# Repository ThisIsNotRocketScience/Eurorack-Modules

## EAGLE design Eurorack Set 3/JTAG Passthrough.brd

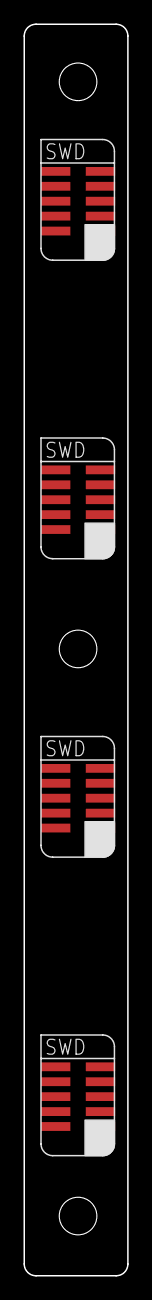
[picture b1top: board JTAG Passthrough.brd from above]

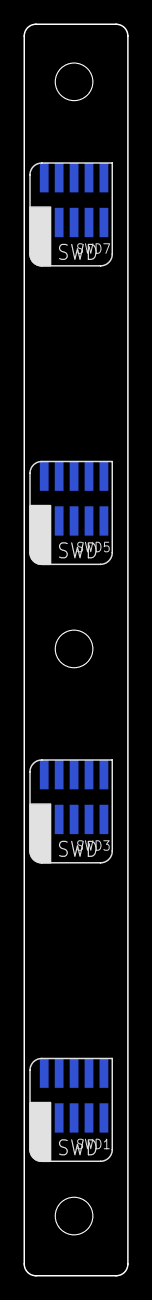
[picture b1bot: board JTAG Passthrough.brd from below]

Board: 2 copper layers, 8.8 x 106.5 mm, 9 parts (4 on the bottom side), 40 nets, no tracks yet.

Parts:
SWD1, SWD3, SWD5, SWD7: CORTEX_SWD; M50-3600542
SWD2, SWD4, SWD6, SWD8: CORTEX_SWDVERT_HOLE; SWD_VERTICAL_WITHHOLE
U$2: EURORACK_PCB2HP; EURORACK2HPPCB

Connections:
unnamed: SWD1.1, SWD2.1
unnamed: SWD1.2, SWD2.2
unnamed: SWD1.3, SWD2.3
unnamed: SWD1.4, SWD2.4
unnamed: SWD1.5, SWD2.5
unnamed: SWD1.6, SWD2.6
unnamed: SWD1.7, SWD2.7
unnamed: SWD1.8, SWD2.8
unnamed: SWD1.9, SWD2.9
unnamed: SWD1.10, SWD2.10
unnamed: SWD3.1, SWD4.1
unnamed: SWD3.2, SWD4.2
unnamed: SWD3.3, SWD4.3
unnamed: SWD3.4, SWD4.4
unnamed: SWD3.5, SWD4.5
unnamed: SWD3.6, SWD4.6
unnamed: SWD3.7, SWD4.7
unnamed: SWD3.8, SWD4.8
unnamed: SWD3.9, SWD4.9
unnamed: SWD3.10, SWD4.10
unnamed: SWD5.1, SWD6.1
unnamed: SWD5.2, SWD6.2
unnamed: SWD5.3, SWD6.3
unnamed: SWD5.4, SWD6.4
unnamed: SWD5.5, SWD6.5
unnamed: SWD5.6, SWD6.6
unnamed: SWD5.7, SWD6.7
unnamed: SWD5.8, SWD6.8
unnamed: SWD5.9, SWD6.9
unnamed: SWD5.10, SWD6.10
unnamed: SWD7.1, SWD8.1
unnamed: SWD7.2, SWD8.2
unnamed: SWD7.3, SWD8.3
unnamed: SWD7.4, SWD8.4
unnamed: SWD7.5, SWD8.5
unnamed: SWD7.6, SWD8.6
unnamed: SWD7.7, SWD8.7
unnamed: SWD7.8, SWD8.8
unnamed: SWD7.9, SWD8.9
unnamed: SWD7.10, SWD8.10

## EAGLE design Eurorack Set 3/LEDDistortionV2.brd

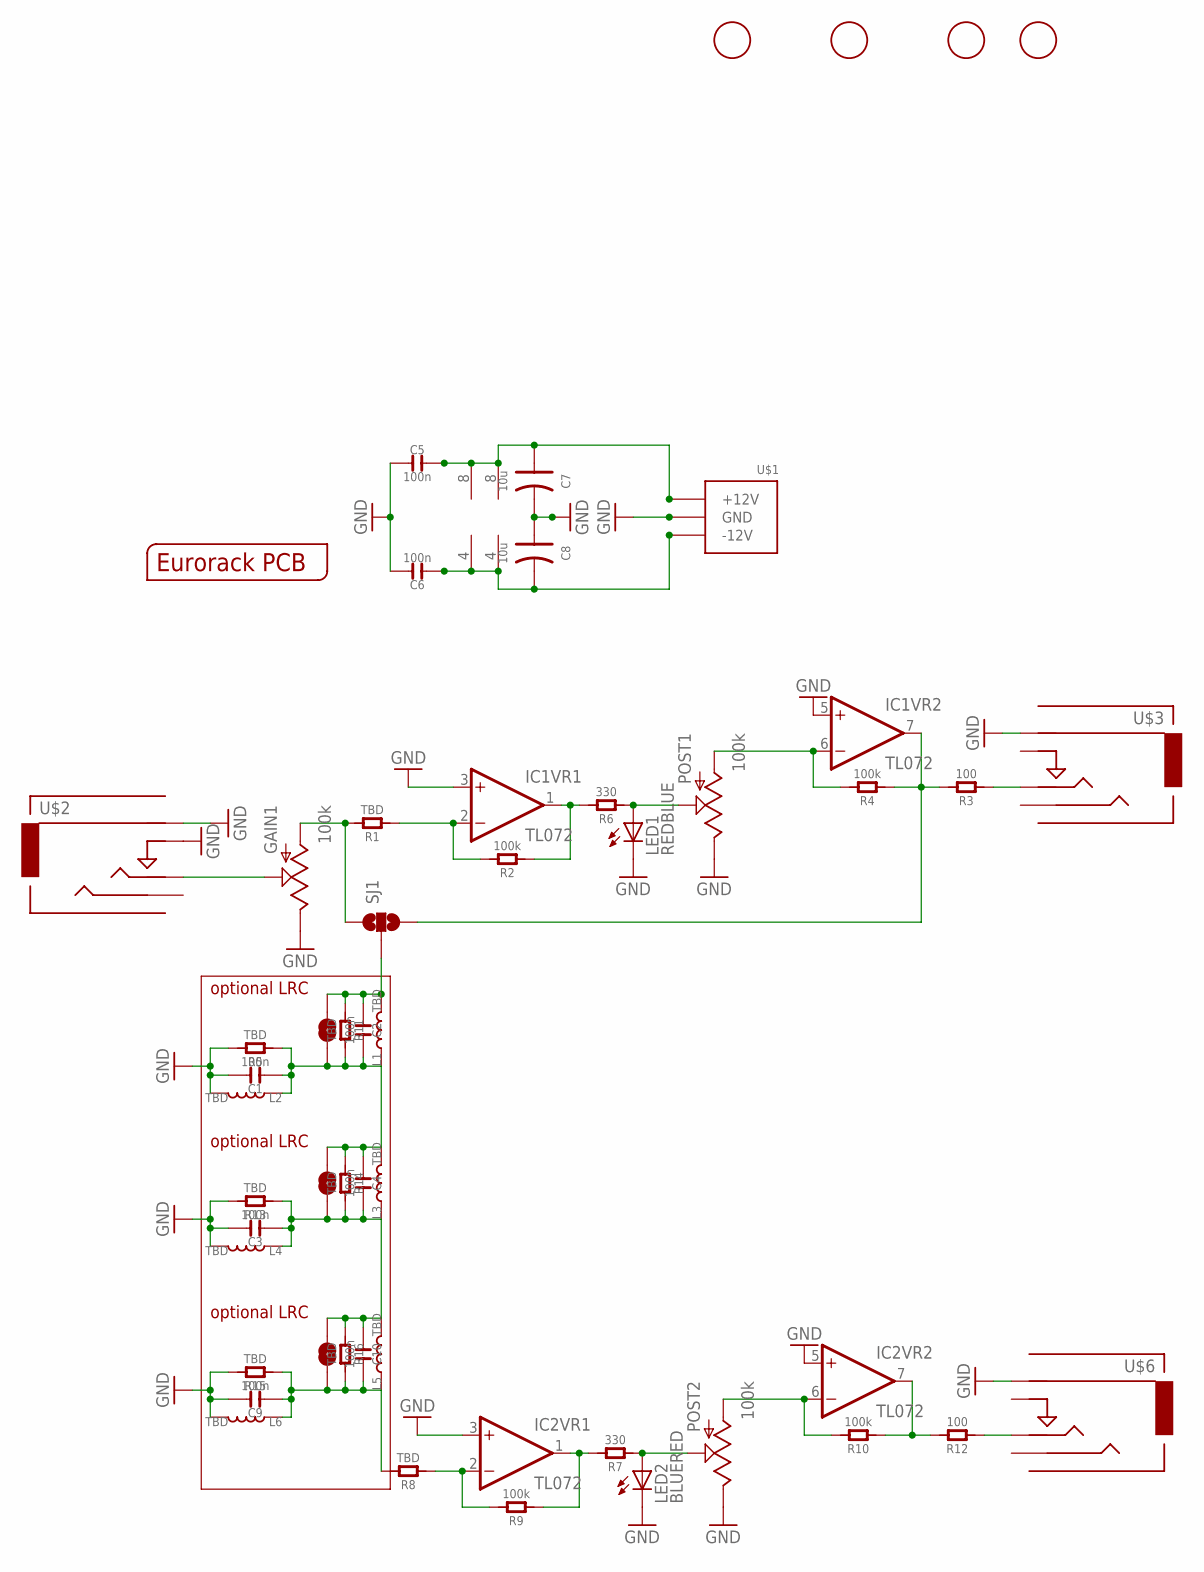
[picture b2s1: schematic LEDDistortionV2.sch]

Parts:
C1, C2, C3, C4, C5, C6, C9, C10: 100n; C0805
C7, C8: 10u; AVX-A
GAIN1: 100k; OG-POTS_ALPS_POT_VERTICAL
IC1, IC2: TL072; SO08
L1, L2, L3, L4, L5, L6: TBD; L0420
LED1: REDBLUE; LED3MM
LED2: BLUERED; LED3MM
POST1, POST2: 100k; OG-POTS_ALPS_POT_VERTICAL
R1, R5, R8, R11, R13, R14, R15, R16: TBD; C0805
R2, R4, R9, R10: 100k; C0805
R3, R12: 100; C0805
R6, R7: 330; C0805
SJ1: SOLDERJUMPER_2WAYPASTE1&2; SJ_3_PASTE1&2
SJ2, SJ3, SJ4: SOLDERJUMPERNC; SJ_2S
U$1: POWER_SIMPLE10; POWER_10
U$2: IN; 3.5MM-JACK-SWITCH-13MM-INPUT
U$3: OUT2; 3.5MM-JACK-SWITCH-13MM-OUTPUT
U$4: EURORACK_PCB4HP; EURORACK4HPPCB
U$5, U$7, U$8, U$9: FIDUCIAL; FIDUCIAL_1MM
U$6: OUT1; 3.5MM-JACK-SWITCH-13MM-OUTPUT

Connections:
GND: C1.2, C3.2, C5.1, C6.2, C7.- (2), C8.+ (1), C9.2, GAIN1.P$1 (E), IC1.3 (+IN), IC1.5 (+IN), IC2.3 (+IN), IC2.5 (+IN), L2.2, L4.2, L6.2, LED1.K (C), LED2.K (C), POST1.P$1 (E), POST2.P$1 (E), R5.2, R13.2, R15.2, U$1.3 (GND), U$1.4 (GND), U$1.5 (GND), U$1.6 (GND), U$1.7 (GND), U$1.8 (GND), U$2.RING@1 (RING), U$2.RING@2 (RING), U$2.SWITCH@1 (SWITCH), U$2.SWITCH@2 (SWITCH), U$3.RING@1 (RING), U$3.RING@2 (RING), U$6.RING@1 (RING), U$6.RING@2 (RING)
unnamed: C2.1, L1.2, R11.1, SJ1.2, SJ2.2
unnamed: LED1.A, POST1.P$2 (S), R6.1
unnamed: GAIN1.P$3 (A), R1.2, SJ1.1
unnamed: IC1.6 (-IN), POST1.P$3 (A), R4.2
unnamed: R3.1, U$3.TIP@1 (TIP), U$3.TIP@2 (TIP)
unnamed: GAIN1.P$2 (S), U$2.TIP@1 (TIP), U$2.TIP@2 (TIP)
unnamed: LED2.A, POST2.P$2 (S), R7.1
unnamed: IC2.6 (-IN), POST2.P$3 (A), R10.2
unnamed: C1.1, C2.2, C4.1, L1.1, L2.1, L3.2, R5.1, R11.2, R14.1, SJ2.1, SJ3.2
unnamed: R12.1, U$6.TIP@1 (TIP), U$6.TIP@2 (TIP)
unnamed: C9.1, C10.2, L5.1, L6.1, R8.2, R15.1, R16.2, SJ4.1
unnamed: C3.1, C4.2, C10.1, L3.1, L4.1, L5.2, R13.1, R14.2, R16.1, SJ3.1, SJ4.2
OP1NEG: IC1.2 (-IN), R1.1, R2.2
OP1NEG1: IC2.2 (-IN), R8.1, R9.2
OP1OUT: IC1.1 (OUT), R2.1, R6.2
OP1OUT1: IC2.1 (OUT), R7.2, R9.1
OP2OUT: IC1.7 (OUT), R3.2, R4.1, SJ1.3
OP2OUT1: IC2.7 (OUT), R10.1, R12.2
VNEG: C6.1, C8.- (2), IC1.4 (V-), IC2.4 (V-), U$1.1 (-12V), U$1.2 (-12V)
VPOS: C5.2, C7.+ (1), IC1.8 (V+), IC2.8 (V+), U$1.9 (+12V), U$1.10 (+12V)

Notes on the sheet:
optional LRC

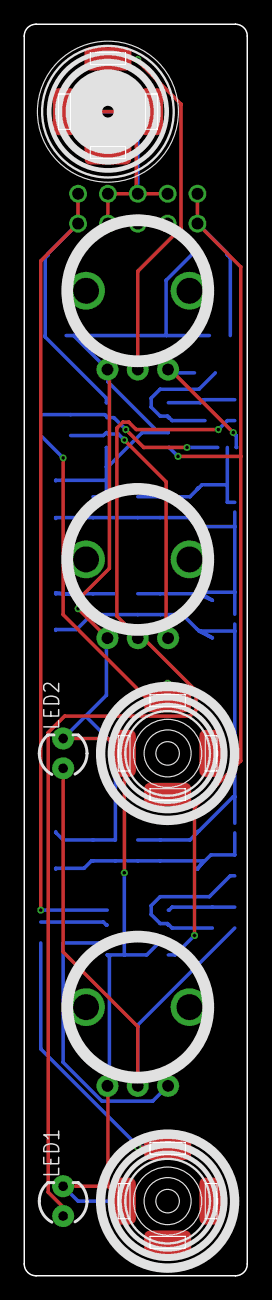
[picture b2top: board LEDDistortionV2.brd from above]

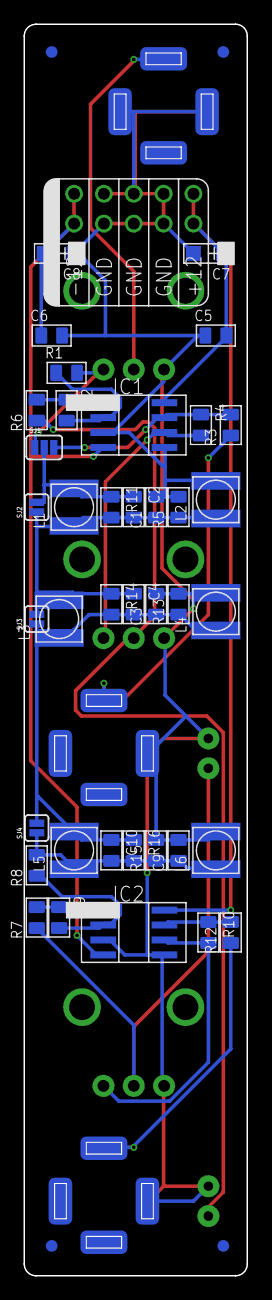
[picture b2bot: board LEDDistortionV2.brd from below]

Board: 2 copper layers, 19.0 x 106.5 mm, 52 parts (43 on the bottom side), 21 nets.

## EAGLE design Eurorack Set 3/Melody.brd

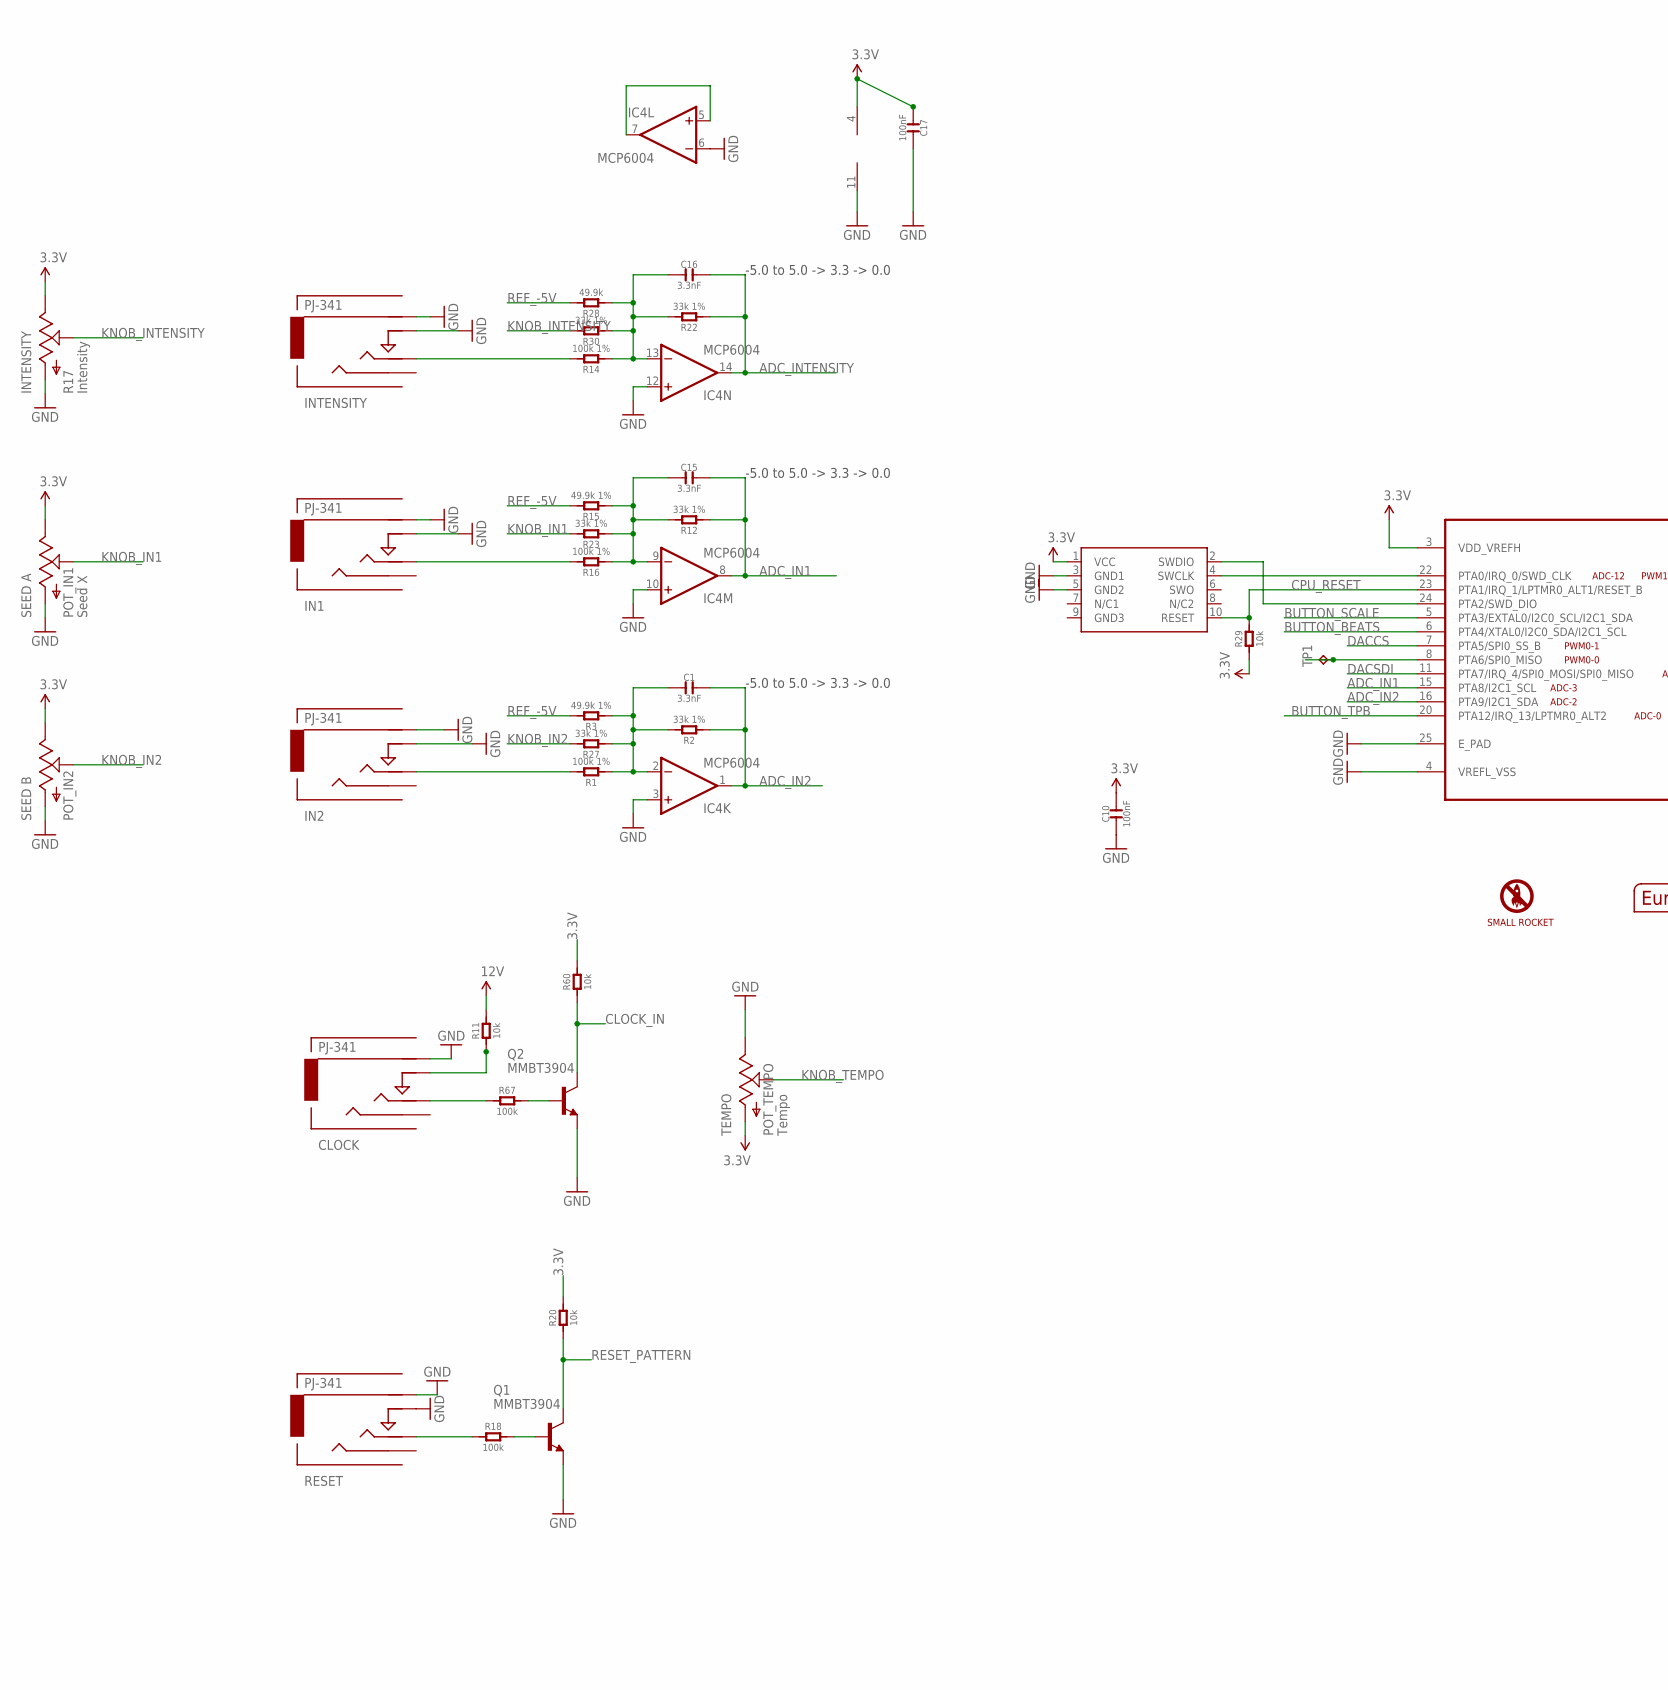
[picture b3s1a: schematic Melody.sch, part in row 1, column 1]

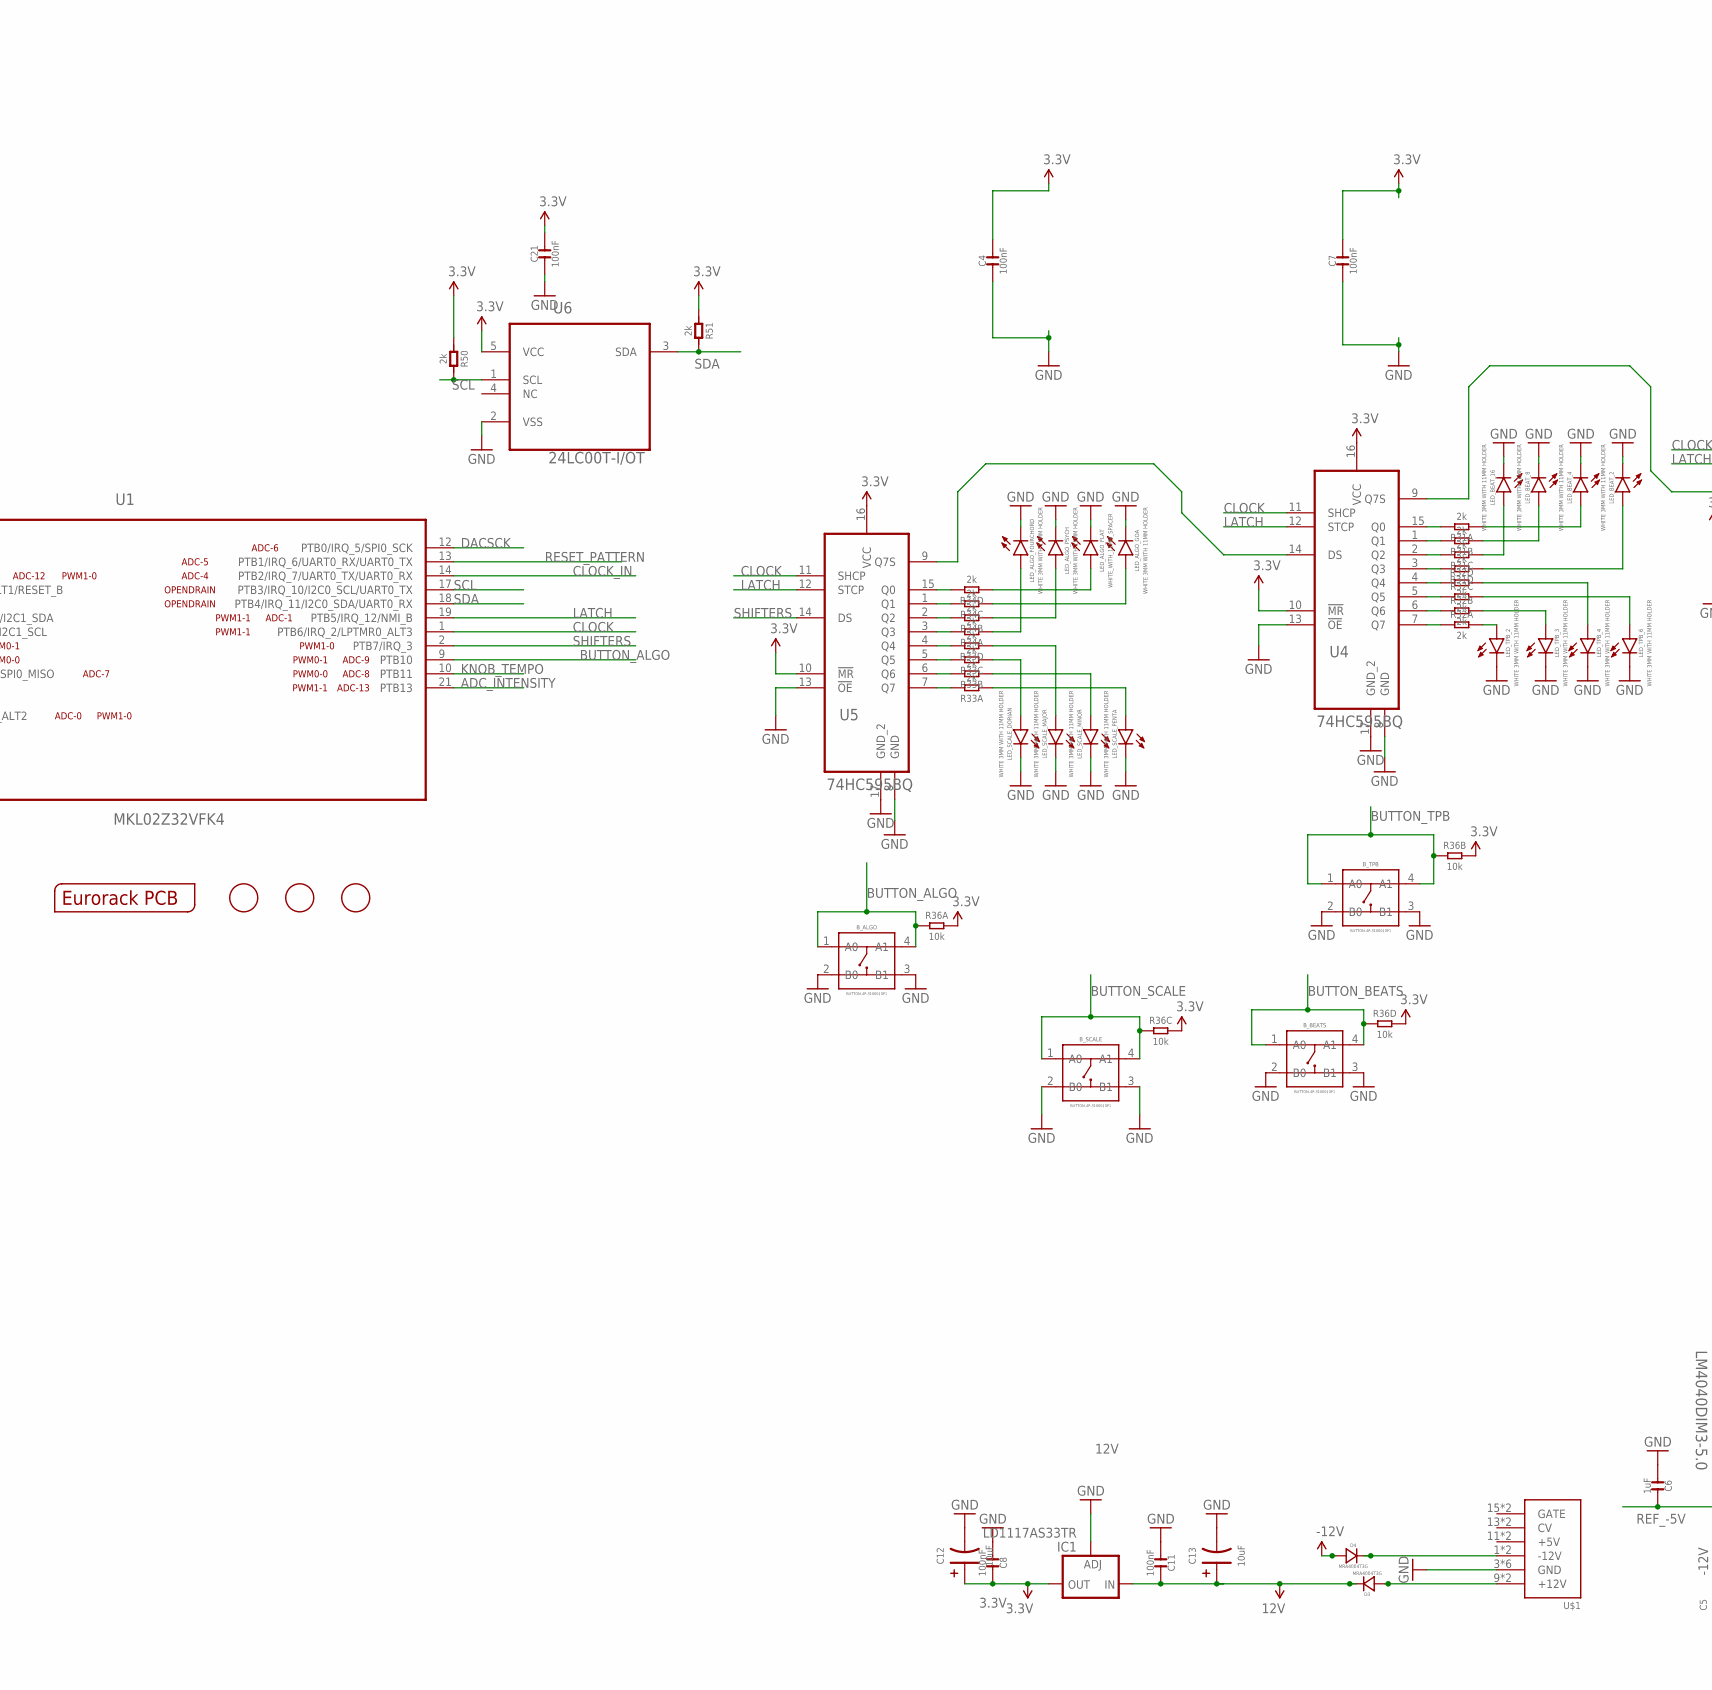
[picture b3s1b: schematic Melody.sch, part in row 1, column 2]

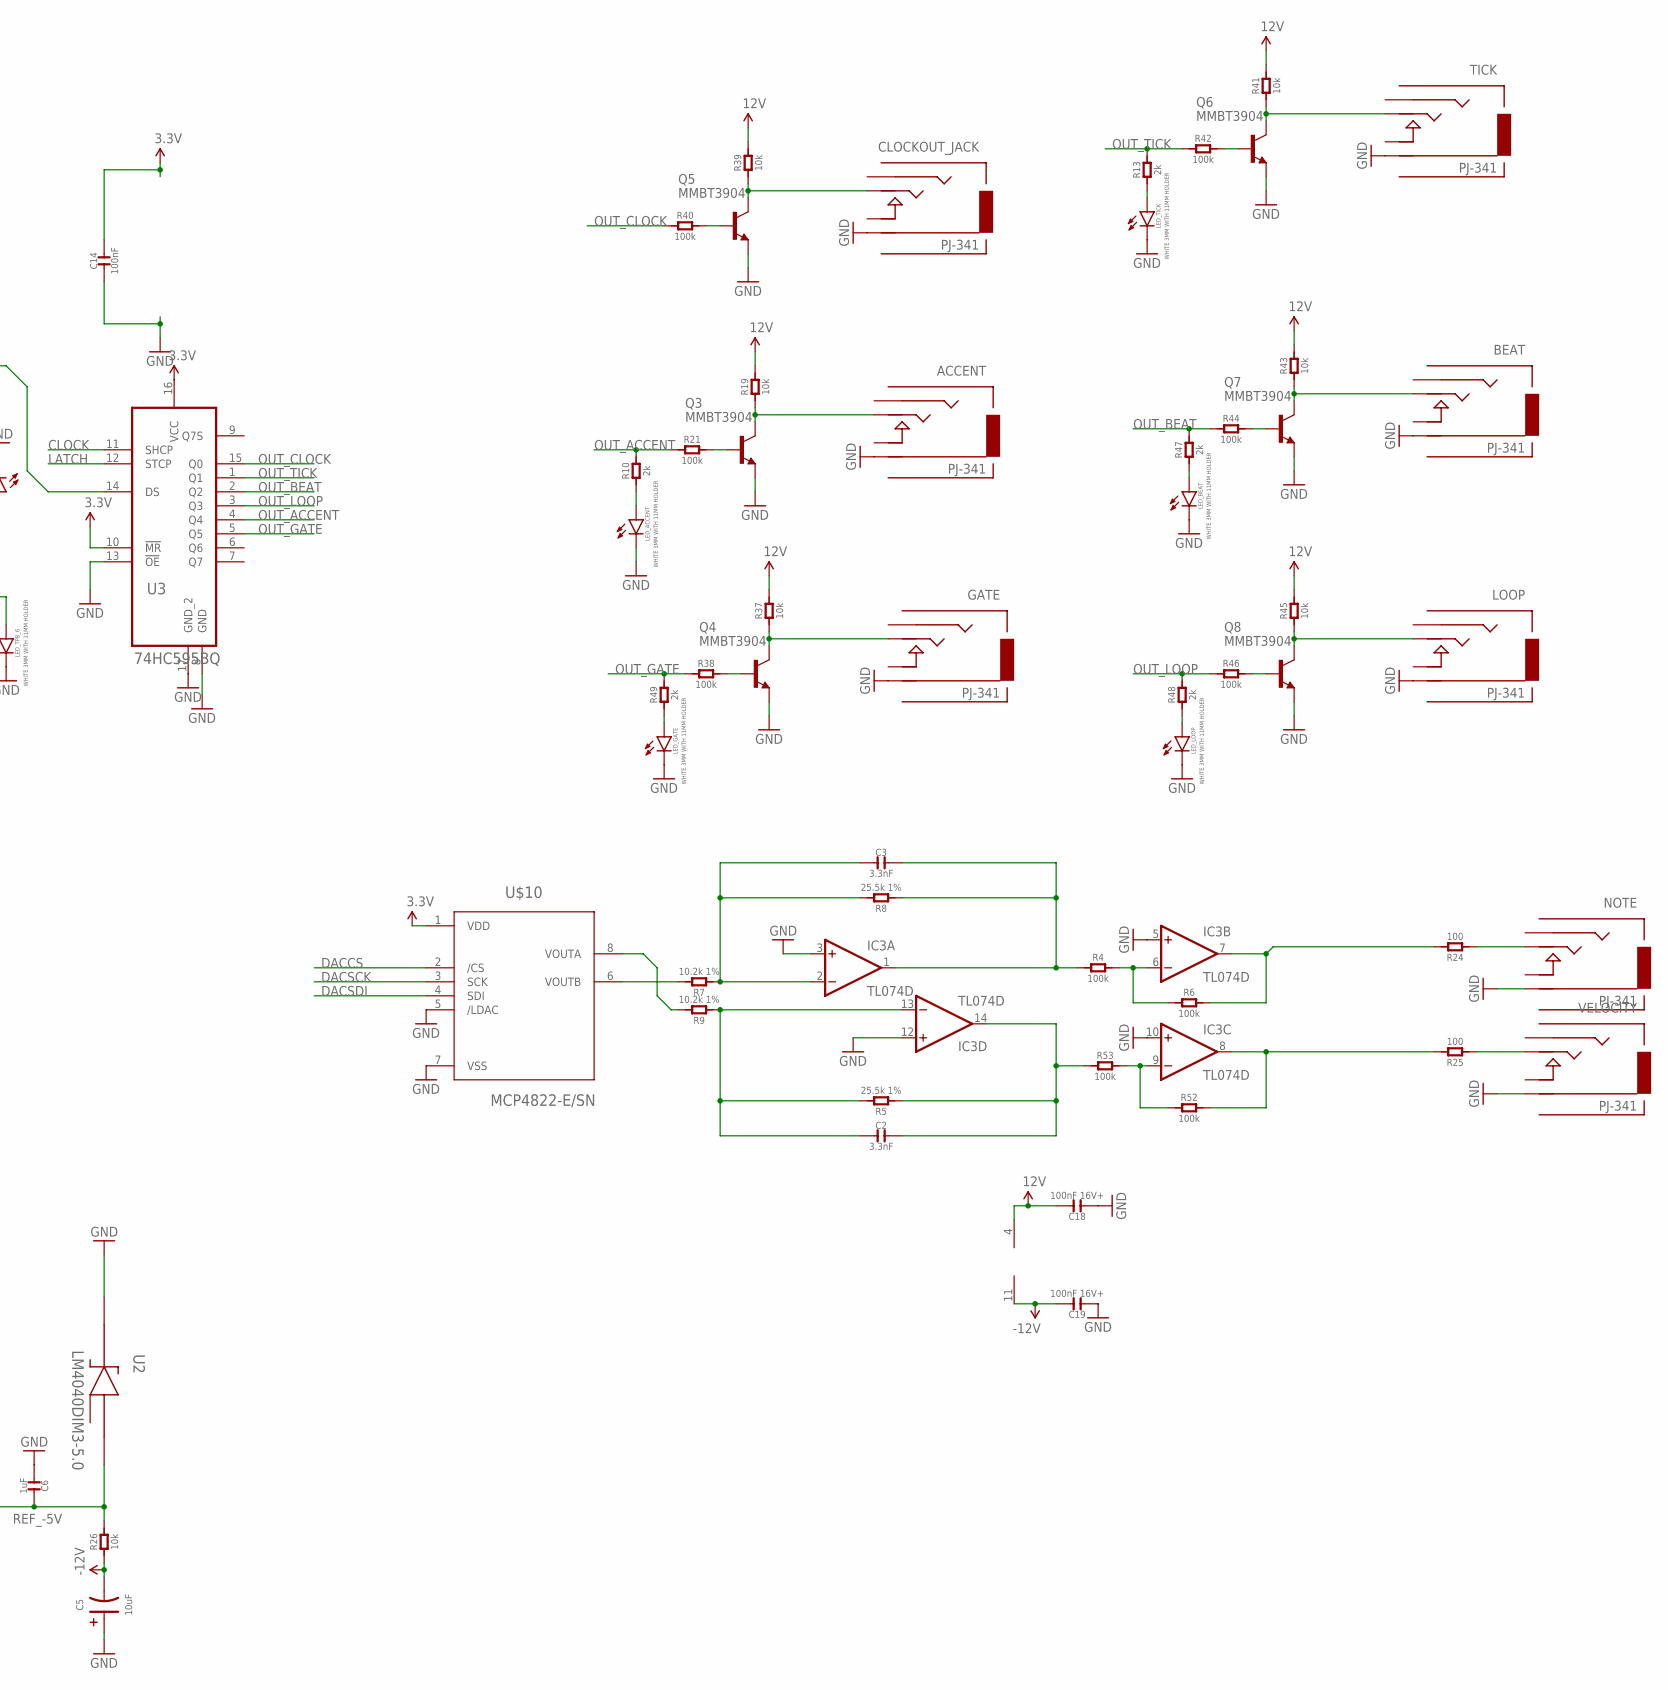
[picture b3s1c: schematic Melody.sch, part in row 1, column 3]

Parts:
ACCENT: PJ-341; 3.5MM-JACK-SWITCH-13MM-OUTPUT
BEAT: PJ-341; 3.5MM-JACK-SWITCH-13MM-OUTPUT
B_ALGO: BUTTON-4P-3100010P1; 4P-SMD-6.0X6.0X5.0H
B_BEATS: BUTTON-4P-3100010P1; 4P-SMD-6.0X6.0X5.0H
B_SCALE: BUTTON-4P-3100010P1; 4P-SMD-6.0X6.0X5.0H
B_TPB: BUTTON-4P-3100010P1; 4P-SMD-6.0X6.0X5.0H
C1, C2, C3, C15, C16: 3.3nF; C0603
C4, C7, C8, C10, C11, C14, C17, C21: 100nF; C0603; MPN MC0603F104Z160CT
C5, C12, C13: 10uF; AVX-A; MPN TAJB106K020RNJ
C6: 1uF; C0603; MPN 06035C104KAT2A
C18, C19: 100nF 16V+; C0603; MPN MC0603F104Z160CT
CLOCK: PJ-341; 3.5MM-JACK-SWITCH-13MM-INPUT
CLOCKOUT_JACK: PJ-341; 3.5MM-JACK-SWITCH-13MM-OUTPUT
D3, D4: MRA4004T3G; DO-214AC; MPN US1G-E3/5AT
GATE: PJ-341; 3.5MM-JACK-SWITCH-13MM-OUTPUT
IC1: LD1117AS33TR; SOT223; MPN LD1117AS33TR
IC3: TL074D; SO14; MPN TL074CD
IC4: MCP6004; SO14; MPN MCP6004-I/SL.
IN1, IN2: PJ-341; 3.5MM-JACK-SWITCH-13MM-INPUT
INTENSITY: PJ-341; 3.5MM-JACK-SWITCH-13MM-INPUT
LED_ACCENT: WHITE 3MM WITH 11MM HOLDER; LED3MM
LED_ALGO_FLAT: WHITE_WITH_11MM_SPACER; LED3MM
LED_ALGO_FOURCHORD: WHITE 3MM WITH 11MM HOLDER; LED3MM
LED_ALGO_GOA: WHITE 3MM WITH 11MM HOLDER; LED3MM
LED_ALGO_PSYCH: WHITE 3MM WITH 11MM HOLDER; LED3MM
LED_BEAT: WHITE 3MM WITH 11MM HOLDER; LED3MM
LED_BEAT_2, LED_BEAT_4, LED_BEAT_8, LED_BEAT_16: WHITE 3MM WITH 11MM HOLDER; LED3MM
LED_GATE: WHITE 3MM WITH 11MM HOLDER; LED3MM
LED_LOOP: WHITE 3MM WITH 11MM HOLDER; LED3MM
LED_SCALE_DORIAN: WHITE 3MM WITH 11MM HOLDER; LED3MM
LED_SCALE_MAJOR: WHITE 3MM WITH 11MM HOLDER; LED3MM
LED_SCALE_MINOR: WHITE 3MM WITH 11MM HOLDER; LED3MM
LED_SCALE_PENTA: WHITE 3MM WITH 11MM HOLDER; LED3MM
LED_TICK: WHITE 3MM WITH 11MM HOLDER; LED3MM
LED_TPB_2, LED_TPB_3, LED_TPB_4, LED_TPB_6: WHITE 3MM WITH 11MM HOLDER; LED3MM
LOOP: PJ-341; 3.5MM-JACK-SWITCH-13MM-OUTPUT
NOTE: PJ-341; 3.5MM-JACK-SWITCH-13MM-OUTPUT
POT_IN1: SEED A; OG-POTS_ALPS_POT_VERTICAL
POT_IN2: SEED B; OG-POTS_ALPS_POT_VERTICAL
POT_TEMPO: TEMPO; OG-POTS_ALPS_POT_VERTICAL
Q1, Q2, Q3, Q4, Q5, Q6, Q7, Q8: MMBT3904; SOT23-BEC; MPN PMBT3904,215
R1, R14, R16: 100k 1%; R0603
R2, R12, R22, R23, R27, R30: 33k 1%; R0603
R3, R15: 49.9k 1%; R0603
R4, R6, R18, R21, R38, R40, R42, R44, R46, R52, R53, R67: 100k; R0603
R5, R8: 25.5k 1%; R0603
R7, R9: 10.2k 1%; R0603
R10, R13, R47, R48, R49, R50, R51: 2k; R0603
R11, R19, R20, R26, R29, R37, R39, R41, R43, R45, R60: 10k; R0603
R17: INTENSITY; OG-POTS_ALPS_POT_VERTICAL
R24, R25: 100; R0603
R28: 49.9k; R0603
R31, R32, R33, R34: 2k; R1206-8
R36: 10k; R1206-8
RESET: PJ-341; 3.5MM-JACK-SWITCH-13MM-INPUT
SWD1: CORTEX_SWD; M50-3600542
TICK: PJ-341; 3.5MM-JACK-SWITCH-13MM-OUTPUT
TP1: TPB1,27; B1,27
U1: MKL02Z32VFK4; QFN50P400X400X100-25N
U2: LM4040DIM3-5.0; SOT95P237X112-3N
U3, U4, U5: 74HC595BQ; QFN50P250X350X100-17N
U6: 24LC00T-I/OT; SOT95P290X145-5N; MPN 24LC00T-I/OT
U$1: POWER; POWER_16
U$2: EURORACK_PCB12HP; EURORACK12HPPCB
U$4, U$7, U$8: FIDUCIAL; FIDUCIAL_1MM
U$10: MCP4822-E/SN; SOIC8-N_MC
U$19: SMALLROCKET
VELOCITY: PJ-341; 3.5MM-JACK-SWITCH-13MM-OUTPUT

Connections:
3.3V: C4.2, C7.2, C8.2, C10.2, C12.+ (1), C14.2, C17.1, C21.2, IC1.2 (OUT), IC1.4 (OUT), IC4.4 (V+), POT_IN1.P$1 (E), POT_IN2.P$1 (E), POT_TEMPO.P$3 (A), R17.P$1 (E), R20.2, R29.1, R36.5 (2), R36.6 (2), R36.7 (2), R36.8 (2), R50.1, R51.1, R60.2, SWD1.1 (VCC), U1.3 (VDD_VREFH), U3.10 (!MR), U3.16 (VCC), U4.10 (!MR), U4.16 (VCC), U5.10 (!MR), U5.16 (VCC), U6.5 (VCC), U$10.1 (VDD)
12V: C11.2, C13.+ (1), C18.2, D3.2 (-), IC1.3 (IN), IC3.4 (V+), R11.2, R19.2, R37.2, R39.2, R41.2, R43.2, R45.2
-12V: C5.- (2), C19.2, D4.1 (+), IC3.11 (V-), R26.1
ADC_IN1: C15.2, IC4.8 (OUT), R12.1, U1.15 (PTA8/I2C1_SCL)
ADC_IN2: C1.2, IC4.1 (OUT), R2.1, U1.16 (PTA9/I2C1_SDA)
ADC_INTENSITY: C16.2, IC4.14 (OUT), R22.1, U1.21 (PTB13)
BUTTON_ALGO: B_ALGO.1 (A0), B_ALGO.4 (A1), R36.1, U1.9 (PTB10)
BUTTON_BEATS: B_BEATS.1 (A0), B_BEATS.4 (A1), R36.4 (1), U1.6 (PTA4/XTAL0/I2C0_SDA/I2C1_SCL)
BUTTON_SCALE: B_SCALE.1 (A0), B_SCALE.4 (A1), R36.3 (1), U1.5 (PTA3/EXTAL0/I2C0_SCL/I2C1_SDA)
BUTTON_TPB: B_TPB.1 (A0), B_TPB.4 (A1), R36.2 (1), U1.20 (PTA12/IRQ_13/LPTMR0_ALT2)
CLOCK: U1.1 (PTB6/IRQ_2/LPTMR0_ALT3), U3.11 (SHCP), U4.11 (SHCP), U5.11 (SHCP)
CLOCK_IN: Q2.C, R60.1, U1.14 (PTB2/IRQ_7/UART0_TX/UART0_RX)
CPU_RESET: R29.2, SWD1.10 (RESET), U1.23 (PTA1/IRQ_1/LPTMR0_ALT1/RESET_B)
DACCS: U1.7 (PTA5/SPI0_SS_B), U$10.2 (/CS)
DACSCK: U1.12 (PTB0/IRQ_5/SPI0_SCK), U$10.3 (SCK)
DACSDI: U1.11 (PTA7/IRQ_4/SPI0_MOSI/SPI0_MISO), U$10.4 (SDI)
GND: ACCENT.RING@3 (RING), BEAT.RING@3 (RING), B_ALGO.2 (B0), B_ALGO.3 (B1), B_BEATS.2 (B0), B_BEATS.3 (B1), B_SCALE.2 (B0), B_SCALE.3 (B1), B_TPB.2 (B0), B_TPB.3 (B1), C4.1, C5.+ (1), C6.1, C7.1, C8.1, C10.1, C11.1, C12.- (2), C13.- (2), C14.1, C17.2, C18.1, C19.1, C21.1, CLOCK.RING@3 (RING), CLOCKOUT_JACK.RING@3 (RING), GATE.RING@3 (RING), IC1.1 (ADJ), IC3.3 (+IN), IC3.5 (+IN), IC3.10 (+IN), IC3.12 (+IN), IC4.3 (+IN), IC4.6 (-IN), IC4.10 (+IN), IC4.11 (V-), IC4.12 (+IN), IN1.RING@3 (RING), IN1.SWITCH@3 (SWITCH), IN2.RING@3 (RING), IN2.SWITCH@3 (SWITCH), INTENSITY.RING@3 (RING), INTENSITY.SWITCH@3 (SWITCH), LED_ACCENT.K (C), LED_ALGO_FLAT.K (C), LED_ALGO_FOURCHORD.K (C), LED_ALGO_GOA.K (C), LED_ALGO_PSYCH.K (C), LED_BEAT.K (C), LED_BEAT_2.K (C), LED_BEAT_4.K (C), LED_BEAT_8.K (C), LED_BEAT_16.K (C), LED_GATE.K (C), LED_LOOP.K (C), LED_SCALE_DORIAN.K (C), LED_SCALE_MAJOR.K (C), LED_SCALE_MINOR.K (C), LED_SCALE_PENTA.K (C), LED_TICK.K (C), LED_TPB_2.K (C), LED_TPB_3.K (C), LED_TPB_4.K (C), LED_TPB_6.K (C), LOOP.RING@3 (RING), NOTE.RING@3 (RING), POT_IN1.P$3 (A), POT_IN2.P$3 (A), POT_TEMPO.P$1 (E), Q1.E, Q2.E, Q3.E, Q4.E, Q5.E, Q6.E, Q7.E, Q8.E, R17.P$3 (A), RESET.RING@3 (RING), RESET.SWITCH@3 (SWITCH), SWD1.3 (GND1), SWD1.5 (GND2), TICK.RING@3 (RING), U1.4 (VREFL_VSS), U1.25 (E_PAD), U2.1 (CATHODE), U3.8 (GND), U3.13 (!OE), U3.17 (GND_2), U4.8 (GND), U4.13 (!OE), U4.17 (GND_2), U5.8 (GND), U5.13 (!OE), U5.17 (GND_2), U6.2 (VSS), U$1.3 (GND), U$1.4 (GND), U$1.5 (GND), U$1.6 (GND), U$1.7 (GND), U$1.8 (GND), U$10.5 (/LDAC), U$10.7 (VSS), VELOCITY.RING@3 (RING)
KNOB_IN1: POT_IN1.P$2 (S), R23.2
KNOB_IN2: POT_IN2.P$2 (S), R27.2
KNOB_INTENSITY: R17.P$2 (S), R30.2
KNOB_TEMPO: POT_TEMPO.P$2 (S), U1.10 (PTB11)
LATCH: U1.19 (PTB5/IRQ_12/NMI_B), U3.12 (STCP), U4.12 (STCP), U5.12 (STCP)
unnamed: R31.7 (2), U4.1 (Q1)
unnamed: IC3.6 (-IN), R4.2, R6.1
unnamed: IN1.TIP@3 (TIP), R16.2
unnamed: C15.1, IC4.9 (-IN), R12.2, R15.1, R16.1, R23.1
unnamed: R9.2, U$10.8 (VOUTA)
unnamed: IN2.TIP@3 (TIP), R1.2
unnamed: R7.2, U$10.6 (VOUTB)
unnamed: C1.1, IC4.2 (-IN), R1.1, R2.2, R3.1, R27.1
unnamed: C2.1, IC3.13 (-IN), R5.2, R9.1
unnamed: C3.1, IC3.2 (-IN), R7.1, R8.2
unnamed: D3.1 (+), U$1.9 (+12V), U$1.10 (+12V)
unnamed: IC3.7 (OUT), R6.2, R24.2
unnamed: Q1.B, R18.2
unnamed: R18.1, RESET.TIP@3 (TIP)
unnamed: IC3.9 (-IN), R52.1, R53.2
unnamed: C3.2, IC3.1 (OUT), R4.1, R8.1
unnamed: R31.6 (2), U4.2 (Q2)
unnamed: R25.1, VELOCITY.TIP@3 (TIP)
unnamed: NOTE.TIP@3 (TIP), R24.1
unnamed: C2.2, IC3.14 (OUT), R5.1, R53.1
unnamed: Q3.B, R21.2
unnamed: R31.5 (2), U4.3 (Q3)
unnamed: R32.4 (1), U4.4 (Q4)
unnamed: LED_SCALE_DORIAN.A, R33.6 (2)
unnamed: ACCENT.TIP@3 (TIP), Q3.C, R19.1
unnamed: R32.3 (1), U4.5 (Q5)
unnamed: R32.2 (1), U4.6 (Q6)
unnamed: LED_SCALE_MAJOR.A, R33.5 (2)
unnamed: INTENSITY.TIP@3 (TIP), R14.2
unnamed: C16.1, IC4.13 (-IN), R14.1, R22.2, R28.1, R30.1
unnamed: R32.1, U4.7 (Q7)
unnamed: R31.8 (2), U4.15 (Q0)
unnamed: R34.4 (1), U5.15 (Q0)
unnamed: R34.3 (1), U5.1 (Q1)
unnamed: R34.2 (1), U5.2 (Q2)
unnamed: R34.1, U5.3 (Q3)
unnamed: R33.4 (1), U5.4 (Q4)
unnamed: R33.3 (1), U5.5 (Q5)
unnamed: CLOCK.TIP@3 (TIP), R67.1
unnamed: R33.2 (1), U5.6 (Q6)
unnamed: R33.1, U5.7 (Q7)
unnamed: Q4.B, R38.2
unnamed: GATE.TIP@3 (TIP), Q4.C, R37.1
unnamed: Q5.B, R40.2
unnamed: CLOCKOUT_JACK.TIP@3 (TIP), Q5.C, R39.1
unnamed: Q6.B, R42.2
unnamed: D4.2 (-), U$1.1 (-12V), U$1.2 (-12V)
unnamed: Q6.C, R41.1, TICK.TIP@3 (TIP)
unnamed: Q2.B, R67.2
unnamed: Q7.B, R44.2
unnamed: BEAT.TIP@3 (TIP), Q7.C, R43.1
unnamed: Q8.B, R46.2
unnamed: LOOP.TIP@3 (TIP), Q8.C, R45.1
unnamed: LED_ALGO_GOA.A, R34.6 (2)
unnamed: LED_ALGO_FLAT.A, R34.5 (2)
unnamed: LED_ALGO_PSYCH.A, R34.7 (2)
unnamed: LED_ALGO_FOURCHORD.A, R34.8 (2)
unnamed: LED_SCALE_MINOR.A, R33.7 (2)
unnamed: LED_SCALE_PENTA.A, R33.8 (2)
unnamed: LED_BEAT_16.A, R31.3 (1)
unnamed: LED_BEAT_8.A, R31.2 (1)
unnamed: LED_BEAT_4.A, R31.1
unnamed: LED_BEAT_2.A, R31.4 (1)
unnamed: LED_TPB_2.A, R32.8 (2)
unnamed: LED_TPB_3.A, R32.7 (2)
unnamed: LED_TPB_4.A, R32.5 (2)
unnamed: LED_TPB_6.A, R32.6 (2)
unnamed: U4.14 (DS), U5.9 (Q7S)
unnamed: U3.14 (DS), U4.9 (Q7S)
unnamed: LED_TICK.A, R13.1
unnamed: LED_LOOP.A, R48.1
unnamed: LED_GATE.A, R49.1
unnamed: LED_BEAT.A, R47.1
unnamed: IC3.8 (OUT), R25.2, R52.2
unnamed: LED_ACCENT.A, R10.1
unnamed: CLOCK.SWITCH@3 (SWITCH), R11.1
unnamed: IC4.5 (+IN), IC4.7 (OUT)
OUT_ACCENT: R10.2, R21.1, U3.4 (Q4)
OUT_BEAT: R44.1, R47.2, U3.2 (Q2)
OUT_CLOCK: R40.1, U3.15 (Q0)
OUT_GATE: R38.1, R49.2, U3.5 (Q5)
OUT_LOOP: R46.1, R48.2, U3.3 (Q3)
OUT_TICK: R13.2, R42.1, U3.1 (Q1)
PTA6: TP1.TP, U1.8 (PTA6/SPI0_MISO)
REF_-5V: C6.2, R3.2, R15.2, R26.2, R28.2, U2.2 (ANODE)
RESET_PATTERN: Q1.C, R20.1, U1.13 (PTB1/IRQ_6/UART0_RX/UART0_TX)
SCL: R50.2, U1.17 (PTB3/IRQ_10/I2C0_SCL/UART0_TX), U6.1 (SCL)
SDA: R51.2, U1.18 (PTB4/IRQ_11/I2C0_SDA/UART0_RX), U6.3 (SDA)
SHIFTERS: U1.2 (PTB7/IRQ_3), U5.14 (DS)
SWD_CLK: SWD1.4 (SWCLK), U1.22 (PTA0/IRQ_0/SWD_CLK)
SWD_DIO: SWD1.2 (SWDIO), U1.24 (PTA2/SWD_DIO)

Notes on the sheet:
-5.0 to 5.0 -> 3.3 -> 0.0

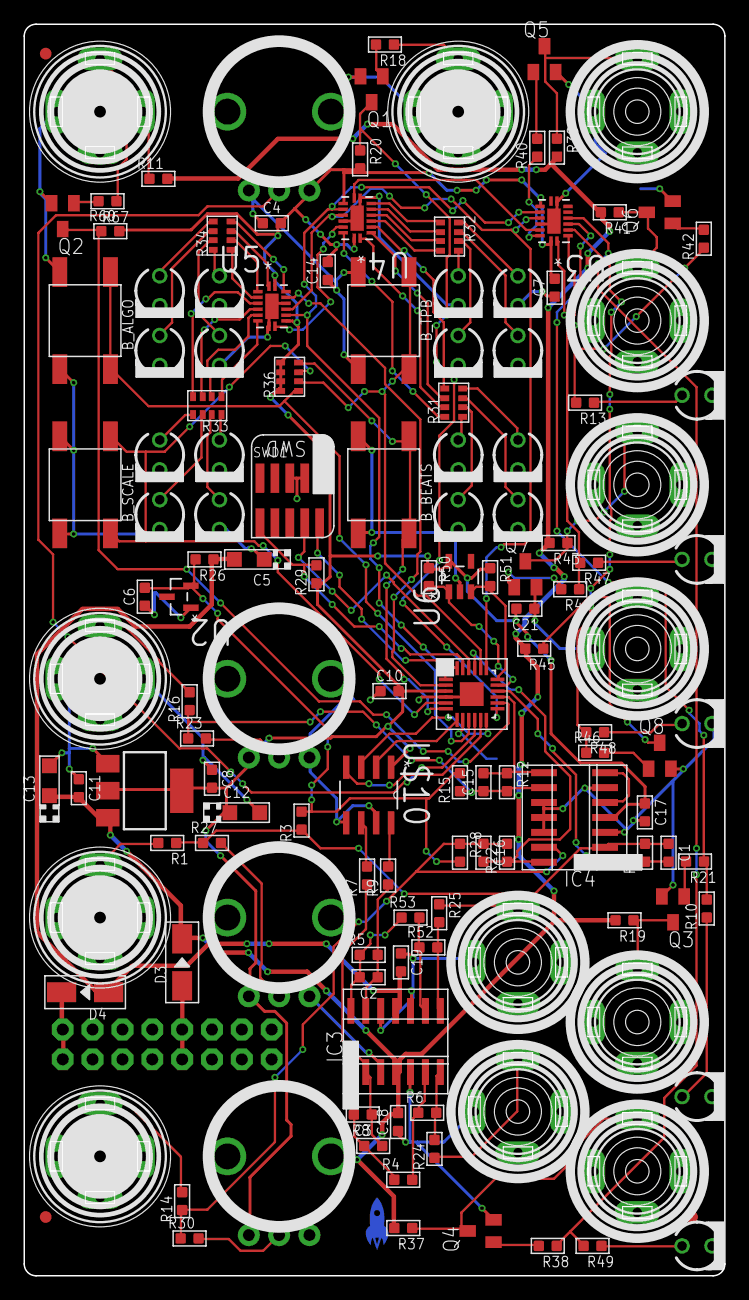
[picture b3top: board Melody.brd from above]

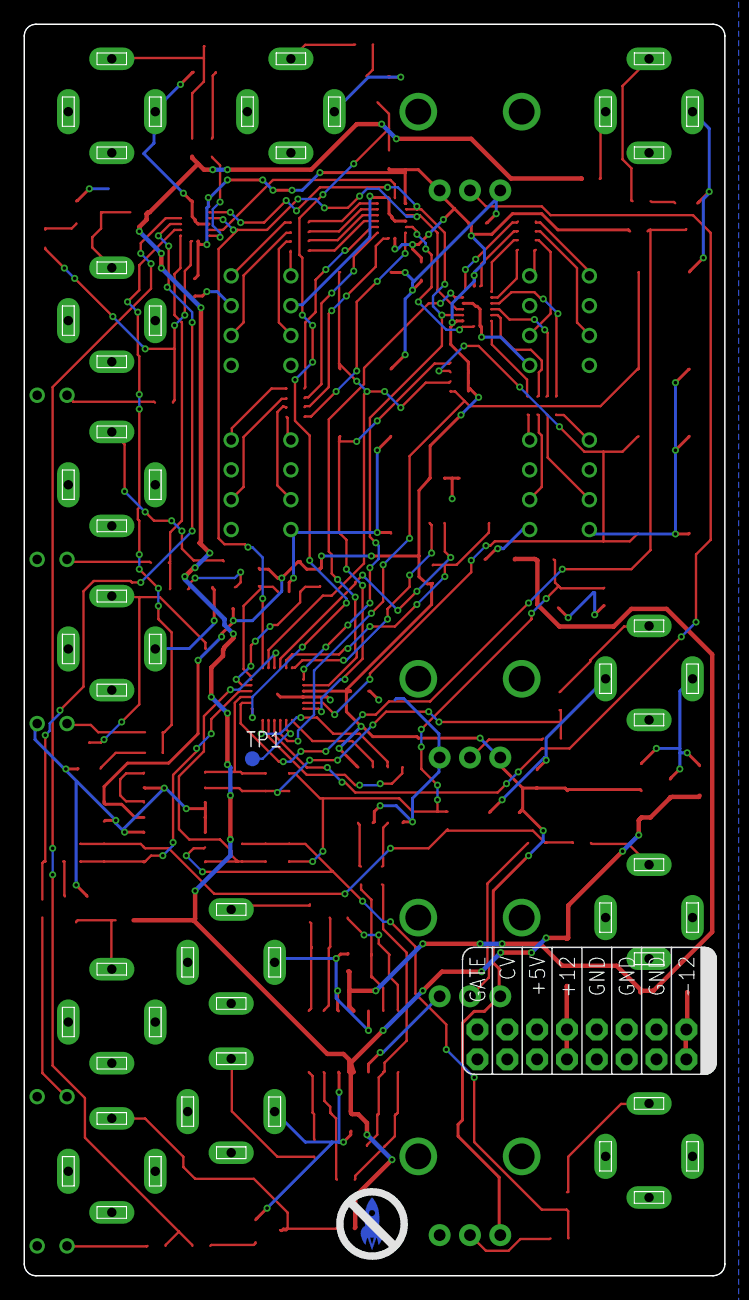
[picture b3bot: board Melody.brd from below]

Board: 2 copper layers, 59.6 x 106.5 mm, 142 parts (3 on the bottom side), 113 nets.

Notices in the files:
parts and their libraries:
SparkFun-LED: Licensing: CC v3.0 Share-Alike You are welcome to use this library for commercial purposes.
